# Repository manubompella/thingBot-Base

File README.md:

# thingBot-Base

thingBot-Base is a universal baseboard designed to program all the thingBot family of devices and can be used 
for peripheral/sensor interfacing as well. Once the thingBots are programmed, Bots can be added to your existing projects
without any worries. 

## thingBot-Base v1.0 Features

  * [XBee Compatible Socket](https://www.sparkfun.com/datasheets/Wireless/Zigbee/XBee-Dimensional.pdf)
  * External 2.54mm header for easier connection to peripherals
  * c-JTAG (10 pin Cortex-M connector) for JTAG debugging the TARGET Bot
  * USB Micro connector (for programming and powering)
  * CP2102 USB to UART Bridge
  * Dual power supply (USB + Li-ion)
  
## thingBot-Base v2.0 Features
  
  * [XBee Compatible Socket](https://www.sparkfun.com/datasheets/Wireless/Zigbee/XBee-Dimensional.pdf)
  * External 2.54mm header for easier connection to peripherals
  * c-JTAG (10 pin Cortex-M connector) for JTAG debugging the TARGET Bot
  * USB Micro connector (for programming and powering)
  * CP2102 USB to UART Bridge
  * Ethernet controller for developing edge-router application
  * Dual power supply with battery charging support
  
## Getting Started

  * Place any thingBot on the XBee Socket as mentioned on the base
  * Connect micro USB cable to the base and your computer
  * Go into the download mode as mentioned in the desired thingBot manual
  * Start code upload and enjoy!!!
  
## Maintainers

The thingBot-Base is maintained by thingTronics Innovations.

Main contributor:
 * Manohar Bompella @<manohar.bompella@thingtronics.com>
 * Vishnu Sherikar @<vishnu.sherikar@thingtronics.com>
 * Lovelesh Patel @<lovelesh.patel@thingtronics.com>

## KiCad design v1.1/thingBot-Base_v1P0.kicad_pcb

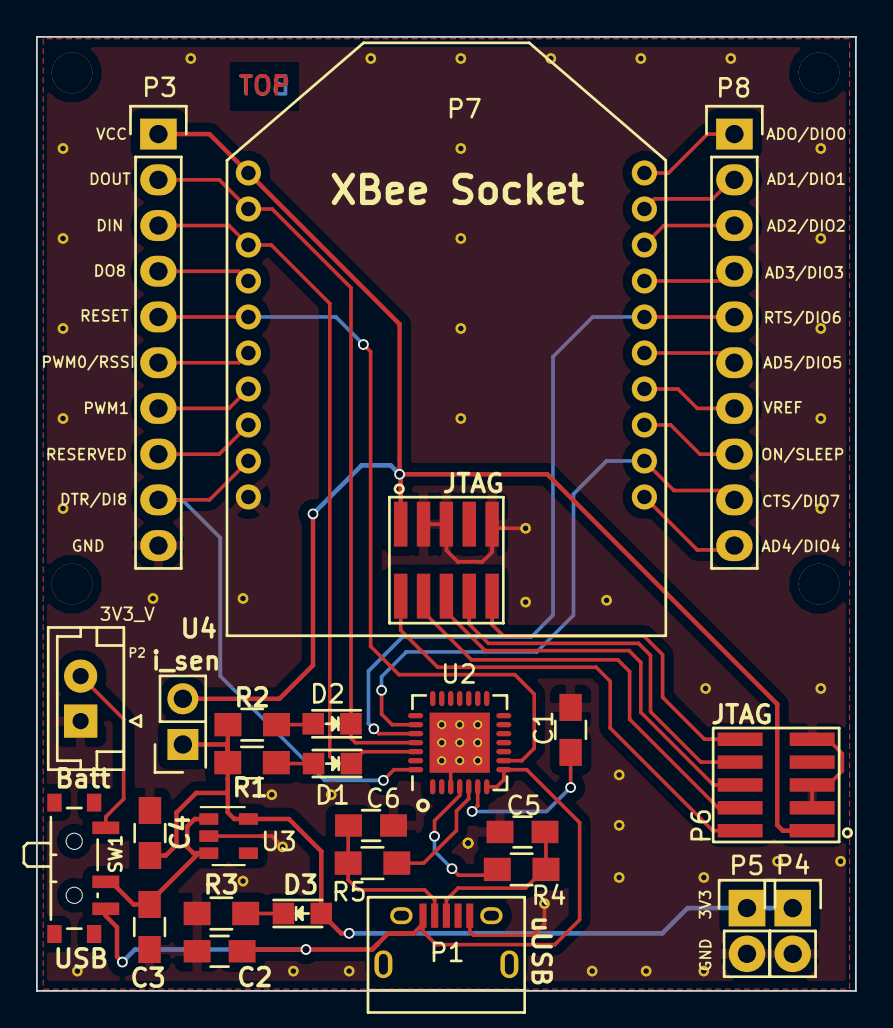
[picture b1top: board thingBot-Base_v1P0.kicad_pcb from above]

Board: 2 copper layers, 45.5 x 53.0 mm, 26 parts (0 on the bottom side), 37 nets.

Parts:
C1: 0.1uF; C_0805_HandSoldering
C2, C3, C4: 1uF; C_0805_HandSoldering
C5, C6: 47pF; C_0805_HandSoldering
D1, D2: YELLOW; LED_0805
D3: POWER; LED_0805
P1: Micro_usb_B; USB_Micro-B
P2: BATT_CONN; JST_EH_B02B-EH-A_02x2.50mm_Straight
P3: XBEE_CONN_LEFT; Pin_Header_Straight_1x10
P4, P5: CONN_01X02; Pin_Header_Straight_1x02
P6: JTAG; Pin_Header_Straight_SMT_02x05_1.27mm_Pitch
P7: XBEE; XBee_Plug
P8: XBEE_CONN_RIGHT; Pin_Header_Straight_1x10
R1, R2, R3: 1K; R_0805_HandSoldering
R4, R5: 27E; R_0805_HandSoldering
SW1: ON/OFF_Switch; SW_SPDT_PCM12
U2: CP2102; QFN-28-1EP_5x5mm_Pitch0.5mm
U3: LP5907_LDO_250mA; SOT-23-5
U4: PROBE; Pin_Header_Straight_2x01

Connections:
+3V3: C4.1, D3.2, P4.1, P5.1, R1.1, R2.1, U3.5, U4.1
+5V: C2.1, P1.1, SW1.3, U2.7, U2.8
/AD0: P7.20, P8.1
/DIN: D1.1, P3.3, P7.3, U2.26
/DOUT: D2.1, P3.2, P7.2, U2.25
CTS: P7.12, P8.9, U2.23
DTR: P3.9, P7.9, U2.28
GND: C1.2, C2.2, C3.2, C4.2, C5.2, C6.2, P1.5, P2.1, P3.10, P4.2, P5.2, P6.3, P6.5, P6.9, P7.10, P7.23, P7.25, P7.29, R3.2, U2.3, U2.29, U3.2
unnamed: C3.1, SW1.2, U3.1, U3.3
unnamed: C5.1, P1.3, R4.2
unnamed: C6.1, P1.2, R5.2
unnamed: D1.2, R1.2
unnamed: D2.2, R2.2
unnamed: D3.1, R3.1
unnamed: P2.2, SW1.1
unnamed: P3.4, P7.4
unnamed: P3.6, P7.6
unnamed: P3.7, P7.7
unnamed: P3.8, P7.8
unnamed: P6.2, P7.22
unnamed: P6.4, P7.24
unnamed: P6.6, P7.26
unnamed: P6.8, P7.28
unnamed: P6.10, P7.30
unnamed: P7.11, P8.10
unnamed: P7.13, P8.8
unnamed: P7.14, P8.7
unnamed: P7.15, P8.6
unnamed: P7.17, P8.4
unnamed: P7.18, P8.3
unnamed: P7.19, P8.2
unnamed: R4.1, U2.4
unnamed: R5.1, U2.5
RST: P3.5, P7.5, U2.9
RTS: P7.16, P8.5, U2.24
VDD: C1.1, U2.6
VXBEE_3V3: P3.1, P6.1, P7.1, P7.21, U4.2

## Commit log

2016-11-24 added directories for PCB schematic design, refrence nad libraries
2016-11-24 added openbase schematic; added sch and project file
2016-11-25 edited README; added FT232 datasheet
2016-11-25 edited README; added tps63051 datasheet
2016-11-27 Complete Schematic Added
    Added Power Section, Usb to Serial Converter Section.
    SPDT switch added for powering the module through Battery and micro USB.
    JTAG Headers included.
    On Board Power indication Led and 3.3v fixed voltage Regulator Added.
2016-11-27 Modified README (#4)
    * edited README with 2 versions of base
    * added battery support
2016-11-27 Libraries Added and some changes made in Schematic
    CP2102 ,probe, AMS117 Libraries added,
    C4,C5 Capacitors Added JTAG gnds connected to Common ground.
2016-11-27 Libraries Added
2016-11-27 updated cp2102 library
2016-11-27 changed README; removed unrequired datasheet
2016-11-28 removed
2016-12-26 Reference files ,bom xl,complete layout added
    following things added
    -reference files
    -complete layout
    -in schematic removed esd protection vbus053a, and added RC circuit
    -lm1117 replaced with lp5907
    -BOM xl sheet added
2016-12-28 final Layout and GERBER creation done
2016-12-29 BOM updated
2016-12-30 version of board added in silkscreen
2017-01-27 thingBot-Base v1.1 all files added
    in v1.1 these thing Added
    - JST connector pins changed
    - 1x2 2.54mm headers alighned properly
